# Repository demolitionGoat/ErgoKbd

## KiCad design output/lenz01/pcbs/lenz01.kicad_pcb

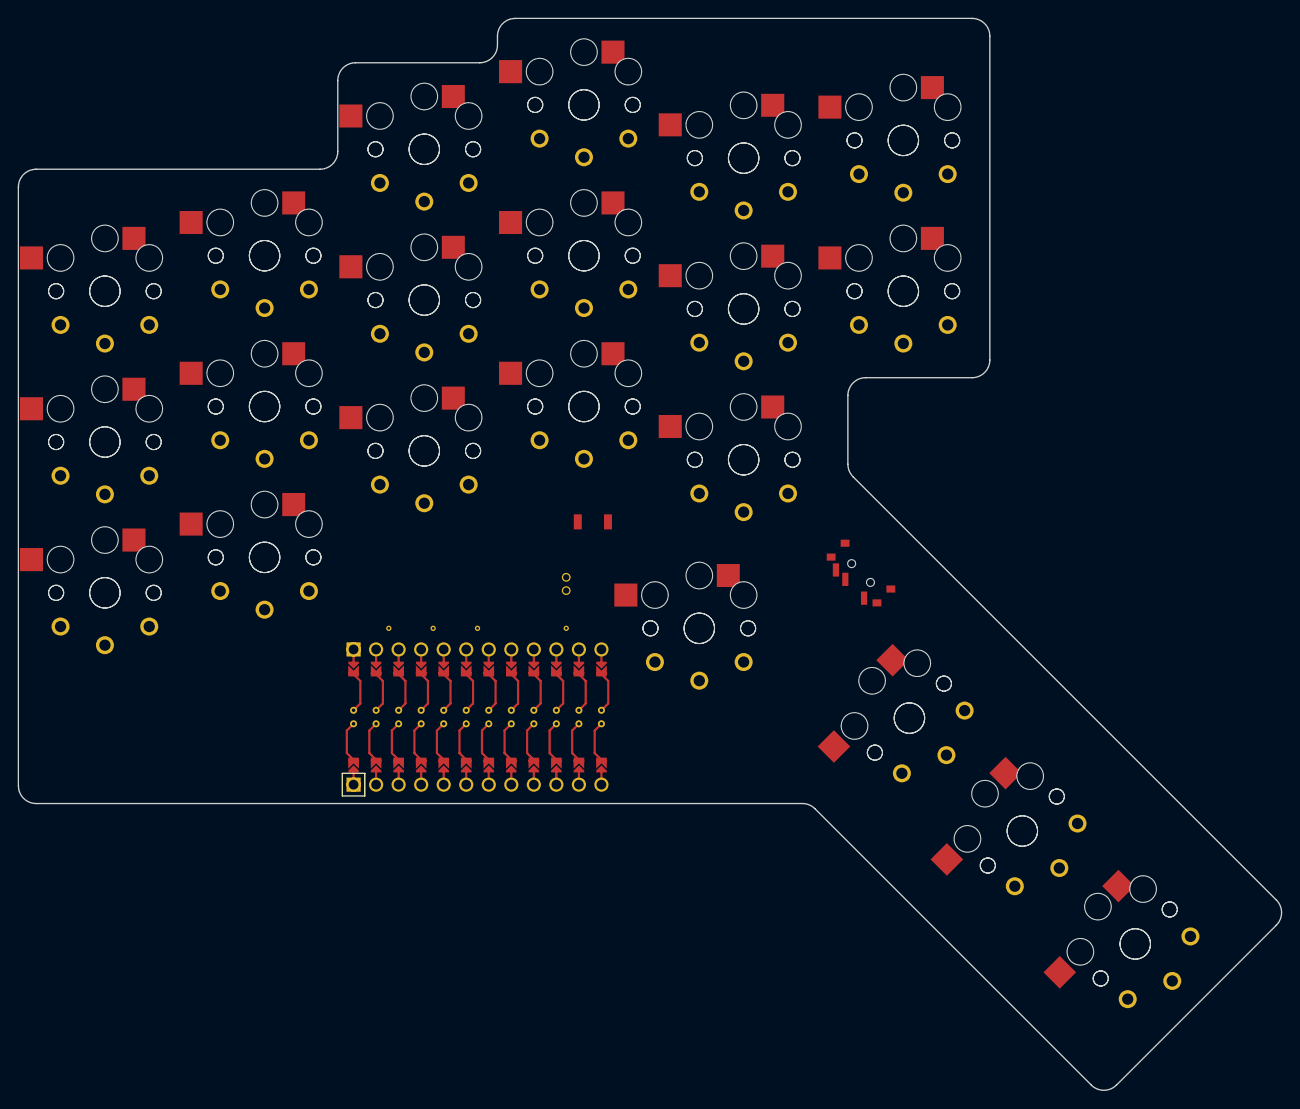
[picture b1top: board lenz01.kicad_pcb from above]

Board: 2 copper layers, 142.4 x 120.8 mm, 43 parts (0 on the bottom side), 14 nets, no tracks yet.

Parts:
MCU1: ProMicro
S1, S2, S3, S4, S5, S6, S7, S8, S9, S10, S11, S12, S13, S14, S15, S16, S17, S18, S19, S20, S21, S22, S23, S24, S25, S26, S27, S28, S29, S30, S31, S32, S33, S34, S35, S36, S37, S38, S39, S40, S41, S42: PG1350

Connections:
GND: MCU1.2, MCU1.21, MCU1.22, S35.2, S36.2, S37.2, S38.2, S39.2, S40.2, S41.2, S42.2
P3: MCU1.19, S1.2, S2.2, S7.2, S8.2, S13.2, S14.2, S19.2, S20.2, S25.2, S26.2
P4: MCU1.18, S3.2, S4.2, S9.2, S10.2, S15.2, S16.2, S21.2, S22.2, S27.2, S28.2, S31.2, S32.2
P5: MCU1.17, S5.2, S6.2, S11.2, S12.2, S17.2, S18.2, S23.2, S24.2, S29.2, S30.2, S33.2, S34.2
P6: MCU1.16, S41.1, S42.1
P7: MCU1.15, S39.1, S40.1
P8: MCU1.14, S37.1, S38.1
P9: MCU1.13, S35.1, S36.1
P10: MCU1.12, S31.1, S32.1, S33.1, S34.1
P14: MCU1.10, S19.1, S20.1, S21.1, S22.1, S23.1, S24.1
P15: MCU1.9, S13.1, S14.1, S15.1, S16.1, S17.1, S18.1
P16: MCU1.11, S25.1, S26.1, S27.1, S28.1, S29.1, S30.1
P20: MCU1.6, S7.1, S8.1, S9.1, S10.1, S11.1, S12.1
P21: MCU1.5, S1.1, S2.1, S3.1, S4.1, S5.1, S6.1

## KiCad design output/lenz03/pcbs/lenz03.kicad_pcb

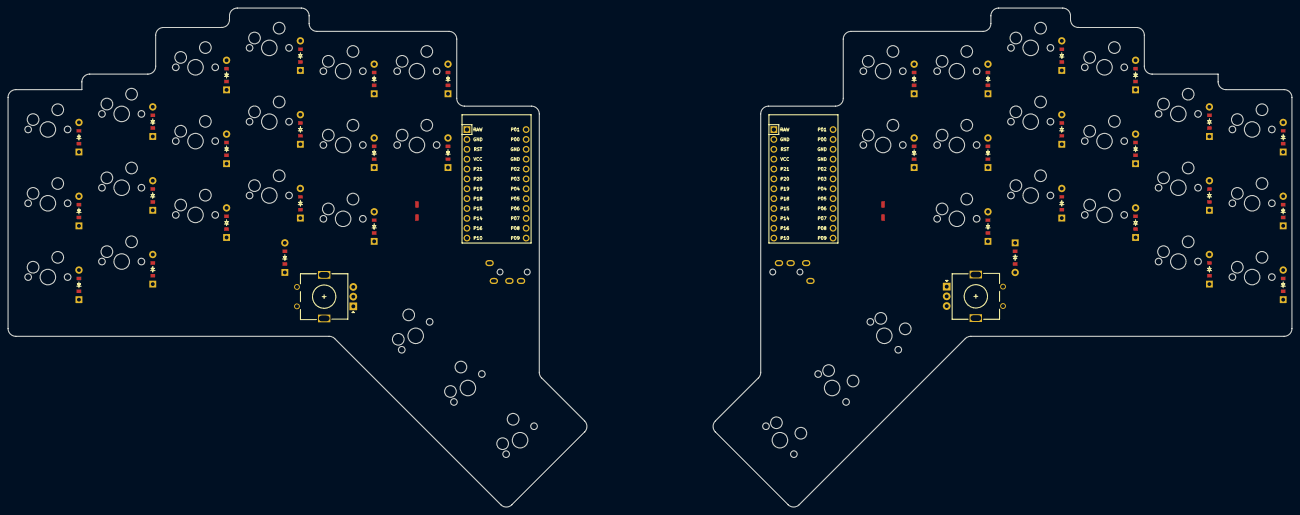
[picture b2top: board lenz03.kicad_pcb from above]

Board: 2 copper layers, 330.5 x 128.4 mm, 80 parts (0 on the bottom side), 58 nets, no tracks yet.

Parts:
D1, D2, D3, D4, D5, D6, D7, D8, D9, D10, D11, D12, D13, D14, D15, D16, D17, D18, D19, D20, D21, D22, D23, D24, D25, D26, D27, D28, D29, D30, D31, D32, D33, D34, D35, D36: ComboDiode
MCU1, MCU2: ProMicro
ROT1, ROT2: rotary_encoder
S1, S2, S3, S4, S5, S6, S7, S8, S9, S10, S11, S12, S13, S14, S15, S16, S17, S18, S19, S20, S21, S22, S23, S24, S25, S26, S27, S28, S29, S30, S31, S32, S33, S34, S35, S36, S37, S38, S39, S40: MX

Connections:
GND: MCU1.2, MCU1.15, MCU1.16, MCU2.2, MCU2.15, MCU2.16, ROT1.B, ROT2.B, S18.2, S19.2, S20.2, S38.2, S39.2, S40.2
P0: MCU1.14, MCU2.14
P1: MCU1.13, MCU2.13
P2: D21.1, D21.2, D24.1, D24.2, D27.1, D27.2, D30.1, D30.2, D33.1, D33.2, D35.1, D35.2, MCU1.17, MCU2.17
P3: D20.1, D20.2, D23.1, D23.2, D26.1, D26.2, D29.1, D29.2, D32.1, D32.2, D34.1, D34.2, MCU1.18, MCU2.18
P4: D19.1, D19.2, D22.1, D22.2, D25.1, D25.2, D28.1, D28.2, D31.1, D31.2, D36.1, D36.2, MCU1.19, MCU2.19, S1.1, S2.1, S3.1
P5: MCU1.20, MCU2.20, ROT1.A, ROT2.1, S36.1, S37.1
P6: MCU1.21, MCU2.21, ROT1.C, S33.1, S34.1, S35.1
P7: MCU1.22, MCU2.22, S18.1, S30.1, S31.1, S32.1, S38.1
P8: MCU1.23, MCU2.23, S19.1, S27.1, S28.1, S29.1, S39.1
P9: MCU1.24, MCU2.24, S20.1, S24.1, S25.1, S26.1, S40.1
P10: MCU1.12, MCU2.12, S4.1, S5.1, S6.1
P14: MCU1.10, MCU2.10, S10.1, S11.1, S12.1
P15: MCU1.9, MCU2.9, ROT2.C, S13.1, S14.1, S15.1
P16: MCU1.11, MCU2.11, S7.1, S8.1, S9.1
P18: MCU1.8, MCU2.8, ROT1.1, ROT2.A, S16.1, S17.1
P19: D1.1, D1.2, D4.1, D4.2, D7.1, D7.2, D10.1, D10.2, D13.1, D13.2, D18.1, D18.2, MCU1.7, MCU2.7, S21.1, S22.1, S23.1
P20: D2.1, D2.2, D5.1, D5.2, D8.1, D8.2, D11.1, D11.2, D14.1, D14.2, D16.1, D16.2, MCU1.6, MCU2.6
P21: D3.1, D3.2, D6.1, D6.2, D9.1, D9.2, D12.1, D12.2, D15.1, D15.2, D17.1, D17.2, MCU1.5, MCU2.5
RAW: MCU1.1, MCU2.1
RST: MCU1.3, MCU2.3
VCC: MCU1.4, MCU2.4
index_bottom: D13.1, D13.2, S13.2
index_home: D14.1, D14.2, S14.2
index_top: D15.1, D15.2, S15.2
middle_bottom: D10.1, D10.2, S10.2
middle_home: D11.1, D11.2, S11.2
middle_top: D12.1, D12.2, S12.2
mirror_index_bottom: D31.1, D31.2, S33.2
mirror_index_home: D32.1, D32.2, S34.2
mirror_index_top: D33.1, D33.2, S35.2
mirror_middle_bottom: D28.1, D28.2, S30.2
mirror_middle_home: D29.1, D29.2, S31.2
mirror_middle_top: D30.1, D30.2, S32.2
mirror_near_home: D36.1, D36.2, ROT2.2
mirror_pinky_bottom: D22.1, D22.2, S24.2
mirror_pinky_home: D23.1, D23.2, S25.2
mirror_pinky_top: D24.1, D24.2, S26.2
mirror_postindex_home: D34.1, D34.2, S36.2
mirror_postindex_top: D35.1, D35.2, S37.2
mirror_prepinky_bottom: D19.1, D19.2, S21.2
mirror_prepinky_home: D20.1, D20.2, S22.2
mirror_prepinky_top: D21.1, D21.2, S23.2
mirror_ring_bottom: D25.1, D25.2, S27.2
mirror_ring_home: D26.1, D26.2, S28.2
mirror_ring_top: D27.1, D27.2, S29.2
near_home: D18.1, D18.2, ROT1.2
pinky_bottom: D4.1, D4.2, S4.2
pinky_home: D5.1, D5.2, S5.2
pinky_top: D6.1, D6.2, S6.2
postindex_home: D16.1, D16.2, S16.2
postindex_top: D17.1, D17.2, S17.2
prepinky_bottom: D1.1, D1.2, S1.2
prepinky_home: D2.1, D2.2, S2.2
prepinky_top: D3.1, D3.2, S3.2
ring_bottom: D7.1, D7.2, S7.2
ring_home: D8.1, D8.2, S8.2
ring_top: D9.1, D9.2, S9.2

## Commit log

2022-09-20 Add files via upload
    fixes
